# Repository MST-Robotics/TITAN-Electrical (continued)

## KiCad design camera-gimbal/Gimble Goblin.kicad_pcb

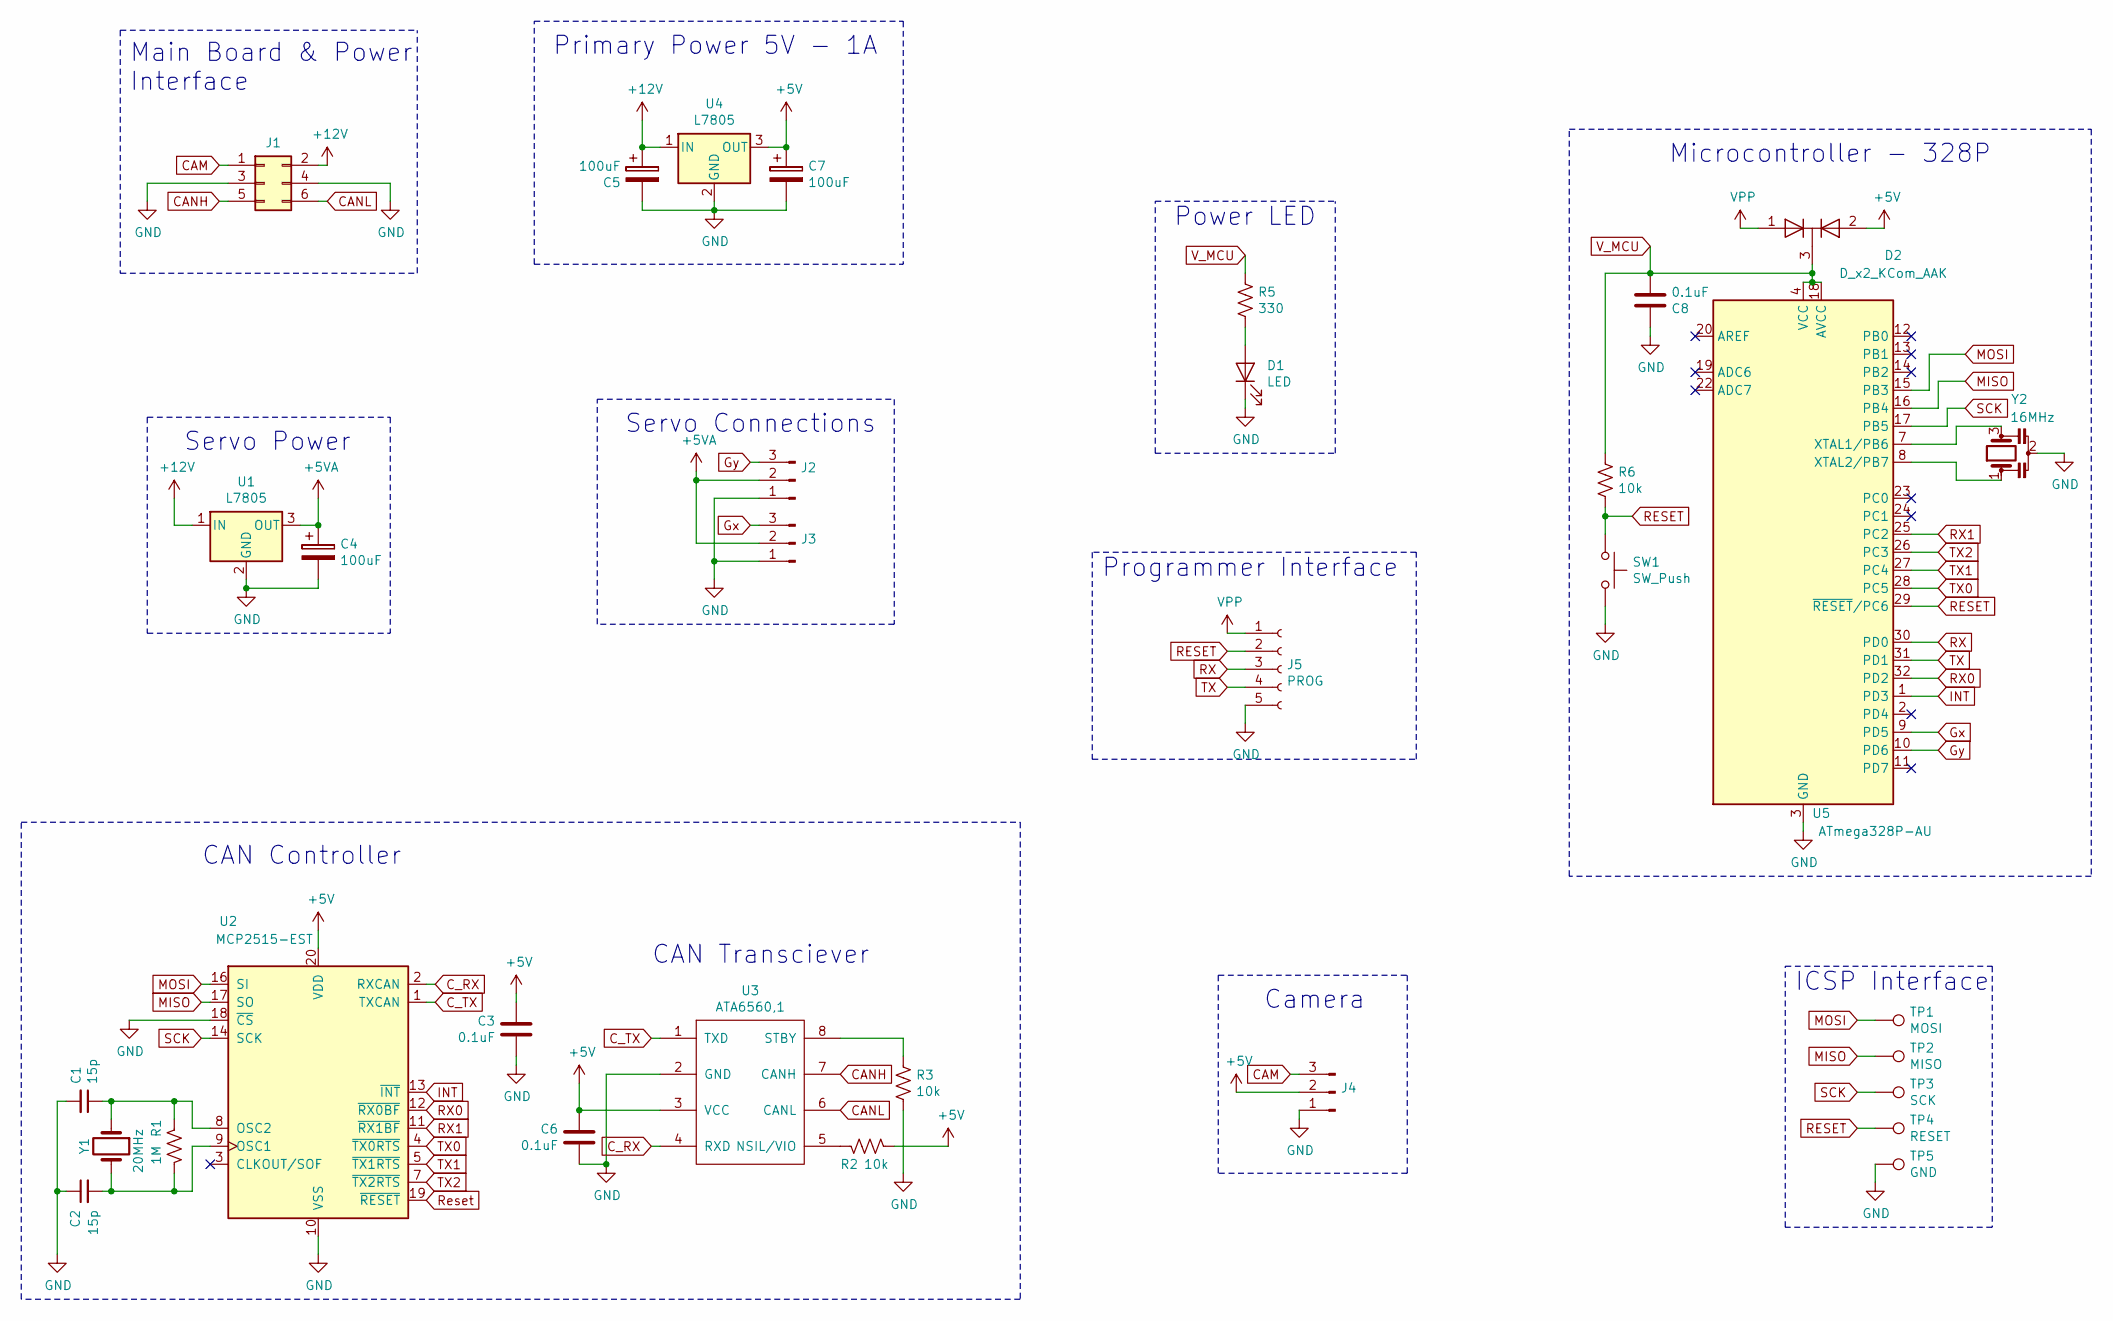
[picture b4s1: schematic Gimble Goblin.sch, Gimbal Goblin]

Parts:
C1, C2: 15p; C_0603_1608Metric
C3, C6, C8: 0.1uF; C_0603_1608Metric
C4, C5, C7: 100uF; CP_Radial_D5.0mm_P2.50mm
D1: LED; LED_0603_1608Metric
D2: D_x2_KCom_AAK; SOT-23
J1: Conn_02x03_Odd_Even; PinHeader_2x03_P2.54mm_Vertical
J2, J3, J4: Conn_01x03_Male; PinHeader_1x03_P2.54mm_Vertical
J5: PROG; PinHeader_1x05_P2.54mm_Vertical
R1: 1M; R_0603_1608Metric
R2, R3, R6: 10k; R_0603_1608Metric
R5: 330; R_0603_1608Metric
SW1: SW_Push; SW_PUSH_6mm
TP1: MOSI; TestPoint_Pad_D1.0mm
TP2: MISO; TestPoint_Pad_D1.0mm
TP3: SCK; TestPoint_Pad_D1.0mm
TP4: RESET; TestPoint_Pad_D1.0mm
TP5: GND; TestPoint_Pad_D1.0mm
U1, U4: L7805; SOT-223
U2: MCP2515-EST; TSSOP-20_4.4x6.5mm_P0.65mm
U3: ATA6560,1; SOIC-8_3.9x4.9mm_P1.27mm
U5: ATmega328P-AU; TQFP-32_7x7mm_P0.8mm
Y1: 20MHz; Crystal_SMD_0603-2Pin_6.0x3.5mm
Y2: 16MHz; OSC_CSTCE16M0V53-R0

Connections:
+5V: C3.2, C6.2, C7.1, D2.2 (A), J4.2, R2.1, U2.20 (VDD), U3.3 (VCC), U4.3 (OUT)
+5VA: C4.1, J2.2, J3.2, U1.3 (OUT)
+12V: C5.1, J1.2, U1.1 (IN), U4.1 (IN)
CAM: J1.1, J4.3
CANH: J1.5, U3.7 (CANH)
CANL: J1.6, U3.6 (CANL)
C_RX: U2.2 (RXCAN), U3.4 (RXD)
C_TX: U2.1 (TXCAN), U3.1 (TXD)
GND: C1.2, C2.1, C3.1, C4.2, C5.2, C6.1, C7.2, C8.2, D1.1 (K), J1.3, J1.4, J2.1, J3.1, J4.1, J5.5, R3.2, SW1.2, TP5.1, U1.2 (GND), U2.10 (VSS), U2.18 (~CS), U3.2 (GND), U4.2 (GND), U5.3 (GND), U5.5 (GND), U5.21 (GND), Y2.2
Gx: J3.3, U5.9 (PD5)
Gy: J2.3, U5.10 (PD6)
INT: U2.13 (~INT), U5.1 (PD3)
MISO: TP2.1, U2.17 (SO), U5.16 (PB4)
MOSI: TP1.1, U2.16 (SI), U5.15 (PB3)
unnamed: C1.1, R1.2, U2.8 (OSC2), Y1.1
unnamed: C2.2, R1.1, U2.9 (OSC1), Y1.2
unnamed: D1.2 (A), R5.2
unnamed: R2.2, U3.5 (NSIL/VIO)
unnamed: R3.1, U3.8 (STBY)
unnamed: U5.7 (XTAL1/PB6), Y2.3
unnamed: U5.8 (XTAL2/PB7), Y2.1
RESET: J5.2, R6.2, SW1.1, TP4.1, U5.29 (~RESET~/PC6)
RX: J5.3, U5.30 (PD0)
RX0: U2.12 (~RX0BF), U5.32 (PD2)
RX1: U2.11 (~RX1BF), U5.25 (PC2)
Reset: U2.19 (~RESET)
SCK: TP3.1, U2.14 (SCK), U5.17 (PB5)
TX: J5.4, U5.31 (PD1)
TX0: U2.4 (~TX0RTS), U5.28 (PC5)
TX1: U2.5 (~TX1RTS), U5.27 (PC4)
TX2: U2.7 (~TX2RTS), U5.26 (PC3)
VPP: D2.1 (A), J5.1
V_MCU: C8.1, D2.3 (K), R5.1, R6.1, U5.4 (VCC), U5.6 (VCC), U5.18 (AVCC)

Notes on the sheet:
Servo Connections
Camera
CAN Controller
CAN Transciever
Main Board & Power Interface
Primary Power 5V - 1A
Servo Power
Microcontroller - 328P
Power LED
Programmer Interface
ICSP Interface

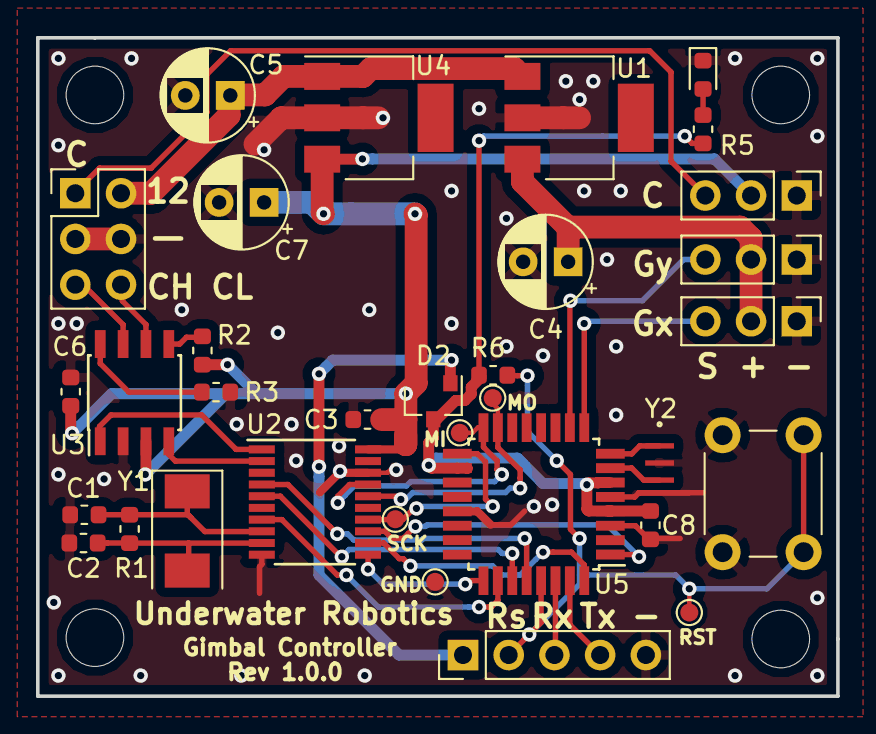
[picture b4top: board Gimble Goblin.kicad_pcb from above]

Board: 2 copper layers, 44.5 x 36.6 mm, 33 parts (0 on the bottom side), 32 nets.

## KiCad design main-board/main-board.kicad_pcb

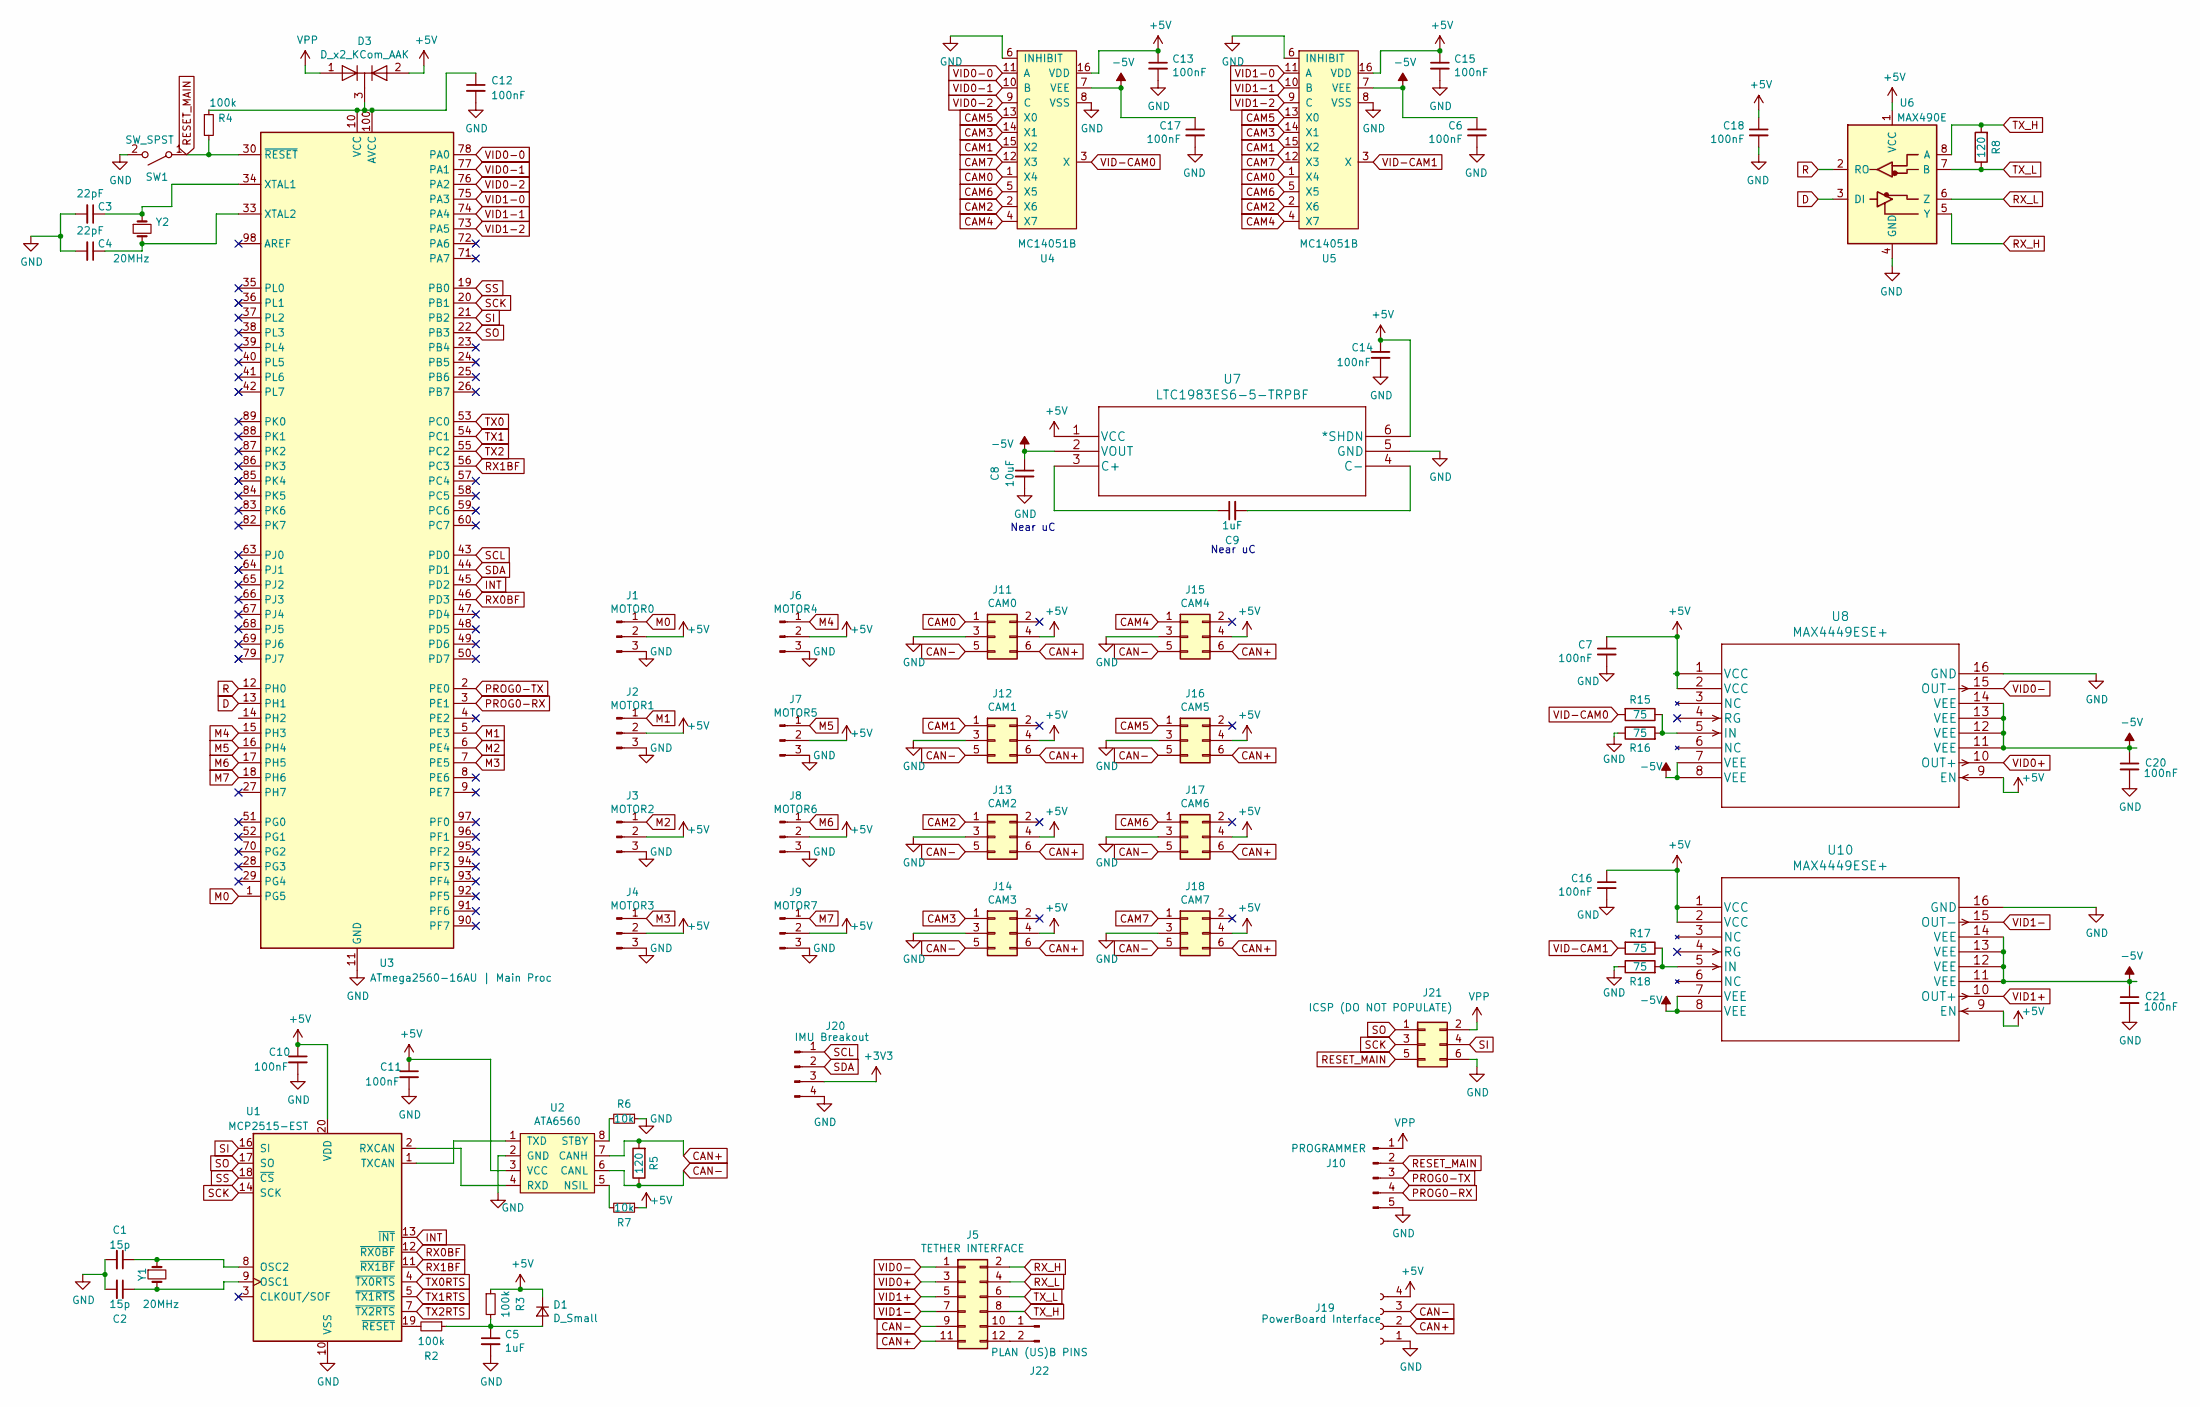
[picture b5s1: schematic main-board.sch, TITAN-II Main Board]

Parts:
C1, C2: 15p; C_0603_1608Metric
C3, C4: 22pF; C_0603_1608Metric
C5, C9: 1uF; C_0603_1608Metric
C6, C7, C10, C11, C12, C13, C14, C15, C16, C17, C18, C20, C21: 100nF; C_0603_1608Metric
C8: 10uF; C_0603_1608Metric
D1: D_Small; D_0603_1608Metric
D3: D_x2_KCom_AAK; SOT-23
J1: MOTOR0; PinHeader_1x03_P2.54mm_Vertical
J2: MOTOR1; PinHeader_1x03_P2.54mm_Vertical
J3: MOTOR2; PinHeader_1x03_P2.54mm_Vertical
J4: MOTOR3; PinHeader_1x03_P2.54mm_Vertical
J5: TETHER INTERFACE; PinHeader_2x06_P2.54mm_Vertical
J6: MOTOR4; PinHeader_1x03_P2.54mm_Vertical
J7: MOTOR5; PinHeader_1x03_P2.54mm_Vertical
J8: MOTOR6; PinHeader_1x03_P2.54mm_Vertical
J9: MOTOR7; PinHeader_1x03_P2.54mm_Vertical
J10: PROGRAMMER; PinHeader_1x05_P2.54mm_Vertical
J11: CAM0; PinHeader_2x03_P2.54mm_Vertical
J12: CAM1; PinHeader_2x03_P2.54mm_Vertical
J13: CAM2; PinHeader_2x03_P2.54mm_Vertical
J14: CAM3; PinHeader_2x03_P2.54mm_Vertical
J15: CAM4; PinHeader_2x03_P2.54mm_Vertical
J16: CAM5; PinHeader_2x03_P2.54mm_Vertical
J17: CAM6; PinHeader_2x03_P2.54mm_Vertical
J18: CAM7; PinHeader_2x03_P2.54mm_Vertical
J19: PowerBoard Interface; PinSocket_1x04_P2.54mm_Vertical
J20: IMU Breakout; PinHeader_1x04_P2.54mm_Vertical
J21: ICSP (DO NOT POPULATE); PinHeader_2x03_P1.00mm_Vertical
J22: PLAN (US)B PINS; PinHeader_1x02_P2.54mm_Vertical
R2, R3, R4: 100k; R_0603_1608Metric
R5, R8: 120; R_0603_1608Metric
R6, R7: 10k; R_0603_1608Metric
R15, R16, R17, R18: 75; R_0603_1608Metric
SW1: SW_SPST; SW_Tactile_Straight_KSA0Axx1LFTR
U1: MCP2515-EST; TSSOP-20_4.4x6.5mm_P0.65mm
U2: ATA6560; SOIC-8_3.9x4.9mm_P1.27mm
U3: ATmega2560-16AU | Main Proc; TQFP-100_14x14mm_P0.5mm
U4, U5: MC14051B; SOIC-16_3.9x9.9mm_P1.27mm
U6: MAX490E; SOIC-8_3.9x4.9mm_P1.27mm
U7: LTC1983ES6-5-TRPBF; SOT-23-6
U8, U10: MAX4449ESE+; MAX4449ESE&plus_
Y1, Y2: 20MHz; Crystal_SMD_Abracon_ABM7-2Pin_6.0x3.5mm

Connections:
+3V3: J20.3
+5V: C7.1, C10.1, C11.1, C13.1, C14.1, C15.1, C16.1, C18.1, D1.1 (K), D3.2 (A), J1.2, J2.2, J3.2, J4.2, J6.2, J7.2, J8.2, J9.2, J11.4, J12.4, J13.4, J14.4, J15.4, J16.4, J17.4, J18.4, J19.4, R3.1, R7.1, U1.20 (VDD), U2.3 (VCC), U4.16 (VDD), U5.16 (VDD), U6.1 (VCC), U7.1 (VCC), U7.6 (*SHDN), U8.1 (VCC), U8.2 (VCC), U8.9 (EN), U10.1 (VCC), U10.2 (VCC), U10.9 (EN)
-5V: C6.1, C8.1, C17.1, C20.1, C21.1, U4.7 (VEE), U5.7 (VEE), U7.2 (VOUT), U8.7 (VEE), U8.8 (VEE), U8.11 (VEE), U8.12 (VEE), U8.13 (VEE), U8.14 (VEE), U10.7 (VEE), U10.8 (VEE), U10.11 (VEE), U10.12 (VEE), U10.13 (VEE), U10.14 (VEE)
CAM0: J11.1, U4.1 (X4), U5.1 (X4)
CAM1: J12.1, U4.15 (X2), U5.15 (X2)
CAM2: J13.1, U4.2 (X6), U5.2 (X6)
CAM3: J14.1, U4.14 (X1), U5.14 (X1)
CAM4: J15.1, U4.4 (X7), U5.4 (X7)
CAM5: J16.1, U4.13 (X0), U5.13 (X0)
CAM6: J17.1, U4.5 (X5), U5.5 (X5)
CAM7: J18.1, U4.12 (X3), U5.12 (X3)
CAN+: J5.11, J11.6, J12.6, J13.6, J14.6, J15.6, J16.6, J17.6, J18.6, J19.2, R5.2, U2.7 (CANH)
CAN-: J5.9, J11.5, J12.5, J13.5, J14.5, J15.5, J16.5, J17.5, J18.5, J19.3, R5.1, U2.6 (CANL)
D: U3.13 (PH1), U6.3 (DI)
GND: C1.2, C2.2, C3.2, C4.2, C5.2, C6.2, C7.2, C8.2, C10.2, C11.2, C12.2, C13.2, C14.2, C15.2, C16.2, C17.2, C18.2, C20.2, C21.2, J1.3, J2.3, J3.3, J4.3, J6.3, J7.3, J8.3, J9.3, J10.5, J11.3, J12.3, J13.3, J14.3, J15.3, J16.3, J17.3, J18.3, J19.1, J20.4, J21.6, R6.1, R16.1, R18.1, SW1.2 (B), U1.10 (VSS), U2.2 (GND), U3.11 (GND), U3.32 (GND), U3.62 (GND), U3.81 (GND), U3.99 (GND), U4.6 (INHIBIT), U4.8 (VSS), U5.6 (INHIBIT), U5.8 (VSS), U6.4 (GND), U7.5 (GND), U8.16 (GND), U10.16 (GND)
INT: U1.13 (~INT), U3.45 (PD2)
M0: J1.1, U3.1 (PG5)
M1: J2.1, U3.5 (PE3)
M2: J3.1, U3.6 (PE4)
M3: J4.1, U3.7 (PE5)
M4: J6.1, U3.15 (PH3)
M5: J7.1, U3.16 (PH4)
M6: J8.1, U3.17 (PH5)
M7: J9.1, U3.18 (PH6)
unnamed: C1.1, U1.8 (OSC2), Y1.1
unnamed: C2.1, U1.9 (OSC1), Y1.2
unnamed: C3.1, U3.34 (XTAL1), Y2.1
unnamed: C4.1, U3.33 (XTAL2), Y2.2
unnamed: C5.1, D1.2 (A), R2.1, R3.2
unnamed: C9.1, U7.3 (C+)
unnamed: C9.2, U7.4 (C-)
unnamed: C12.1, D3.3 (K), R4.1, U3.10 (VCC), U3.31 (VCC), U3.61 (VCC), U3.80 (VCC), U3.100 (AVCC)
unnamed: J5.10, J22.1
unnamed: J5.12, J22.2
unnamed: R2.2, U1.19 (~RESET)
unnamed: R6.2, U2.8 (STBY)
unnamed: R7.2, U2.5 (NSIL)
unnamed: R15.1, R16.2, U8.5 (IN)
unnamed: R17.1, R18.2, U10.5 (IN)
unnamed: U1.1 (TXCAN), U2.1 (TXD)
unnamed: U1.2 (RXCAN), U2.4 (RXD)
PROG0-RX: J10.4, U3.3 (PE1)
PROG0-TX: J10.3, U3.2 (PE0)
R: U3.12 (PH0), U6.2 (RO)
RESET_MAIN: J10.2, J21.5, R4.2, SW1.1 (A), U3.30 (~RESET)
RX0BF: U1.12 (~RX0BF), U3.46 (PD3)
RX1BF: U1.11 (~RX1BF), U3.56 (PC3)
RX_H: J5.2, U6.5 (Y)
RX_L: J5.4, U6.6 (Z)
SCK: J21.3, U1.14 (SCK), U3.20 (PB1)
SCL: J20.1, U3.43 (PD0)
SDA: J20.2, U3.44 (PD1)
SI: J21.4, U1.16 (SI), U3.21 (PB2)
SO: J21.1, U1.17 (SO), U3.22 (PB3)
SS: U1.18 (~CS), U3.19 (PB0)
TX0: U3.53 (PC0)
TX0RTS: U1.4 (~TX0RTS)
TX1: U3.54 (PC1)
TX1RTS: U1.5 (~TX1RTS)
TX2: U3.55 (PC2)
TX2RTS: U1.7 (~TX2RTS)
TX_H: J5.8, R8.2, U6.8 (A)
TX_L: J5.6, R8.1, U6.7 (B)
VID0+: J5.3, U8.10 (OUT+)
VID0-: J5.1, U8.15 (OUT-)
VID0-0: U3.78 (PA0), U4.11 (A)
VID0-1: U3.77 (PA1), U4.10 (B)
VID0-2: U3.76 (PA2), U4.9 (C)
VID1+: J5.5, U10.10 (OUT+)
VID1-: J5.7, U10.15 (OUT-)
VID1-0: U3.75 (PA3), U5.11 (A)
VID1-1: U3.74 (PA4), U5.10 (B)
VID1-2: U3.73 (PA5), U5.9 (C)
VID-CAM0: R15.2, U4.3 (X)
VID-CAM1: R17.2, U5.3 (X)
VPP: D3.1 (A), J10.1, J21.2

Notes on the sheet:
Near uC

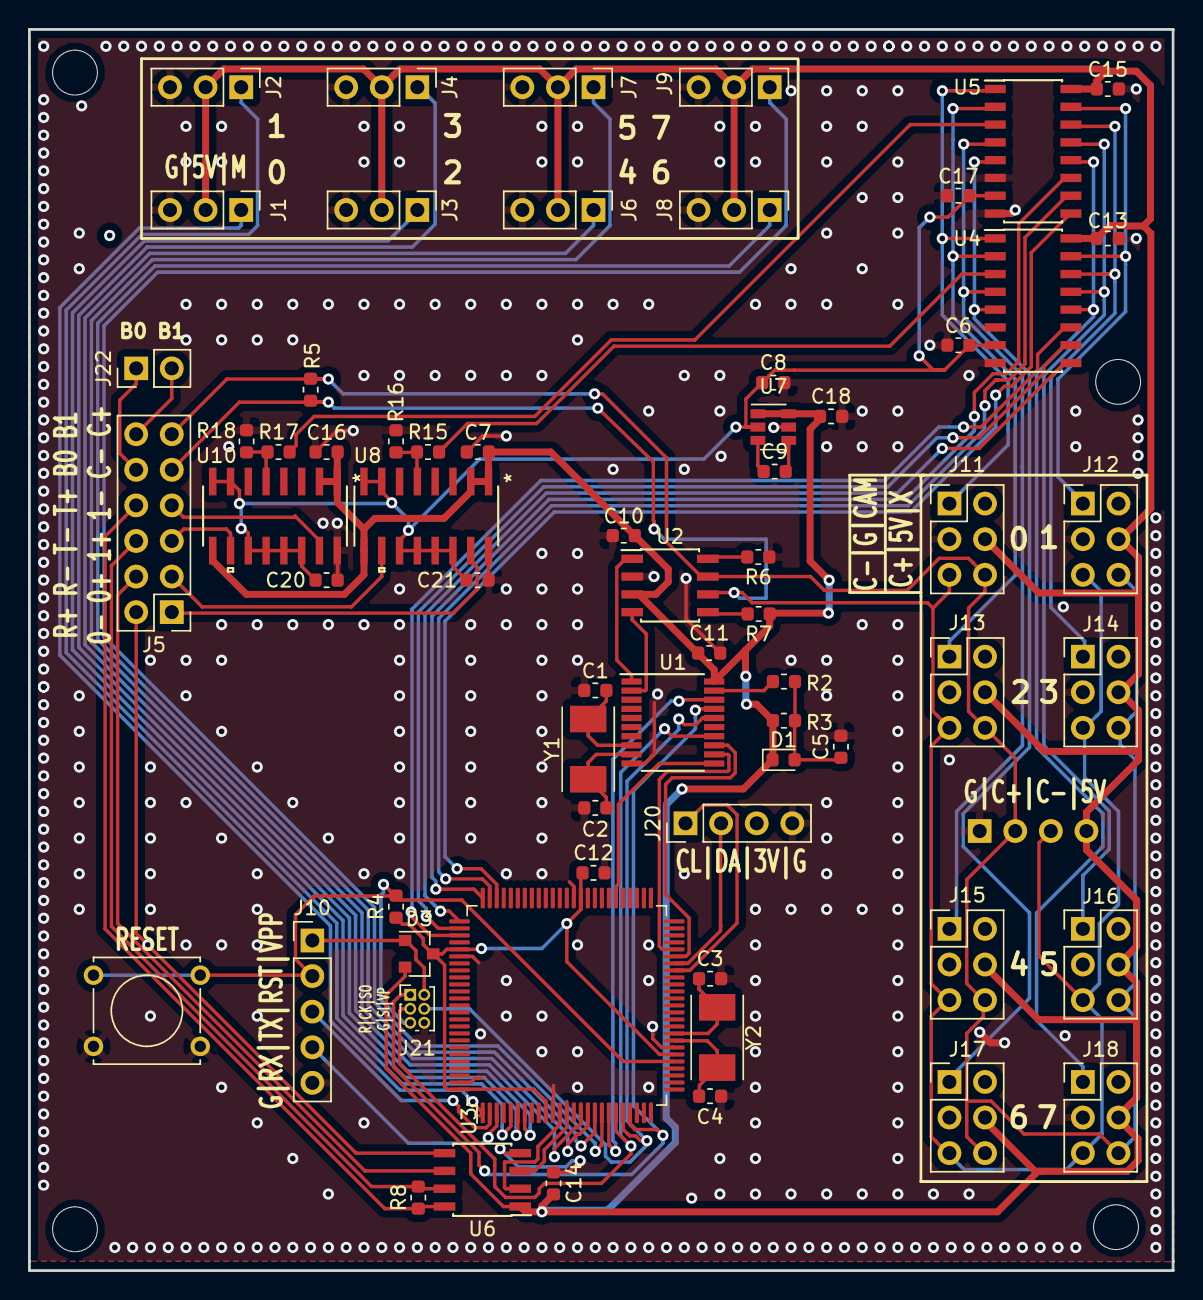
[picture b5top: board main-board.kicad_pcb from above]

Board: 2 copper layers, 81.6 x 88.6 mm, 67 parts (1 on the bottom side), 69 nets.

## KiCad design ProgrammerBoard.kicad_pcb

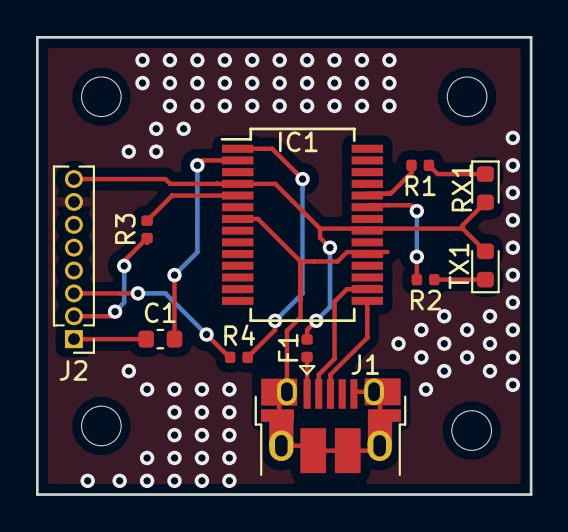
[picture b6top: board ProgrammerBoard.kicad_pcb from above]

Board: 2 copper layers, 27.4 x 25.4 mm, 11 parts (0 on the bottom side), 15 nets.

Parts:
C1: 100nF; C_0603_1608Metric
F1: 500mA; Fuse_0402_1005Metric
IC1: FT232RL; SSOP-28_5.3x10.2mm_P0.65mm
J1: USB_B_Micro; USB_Micro-B_Amphenol_10103594-0001LF_Horizontal
J2: Jumper_For_RJ45; PinHeader_1x08_P1.27mm_Vertical
R1, R2: 1K; R_0402_1005Metric
R3, R4: 100; R_0402_1005Metric
RX1: Blue; LED_0603_1608Metric
TX1: Green; LED_0603_1608Metric

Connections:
+5V: F1.1, IC1.4, IC1.20, J2.8, RX1.2, TX1.2
Earth: IC1.7, IC1.18, IC1.21, IC1.25, IC1.26, J1.5, J1.6
unnamed: C1.1, J2.1
unnamed: C1.2, IC1.2
unnamed: F1.2, J1.1
unnamed: IC1.1, R4.2
unnamed: IC1.5, R3.2
unnamed: IC1.15, J1.3
unnamed: IC1.16, J1.2
unnamed: IC1.22, R2.2
unnamed: IC1.23, R1.2
unnamed: J2.2, R3.1
unnamed: J2.3, R4.1
unnamed: R1.1, RX1.1
unnamed: R2.1, TX1.1

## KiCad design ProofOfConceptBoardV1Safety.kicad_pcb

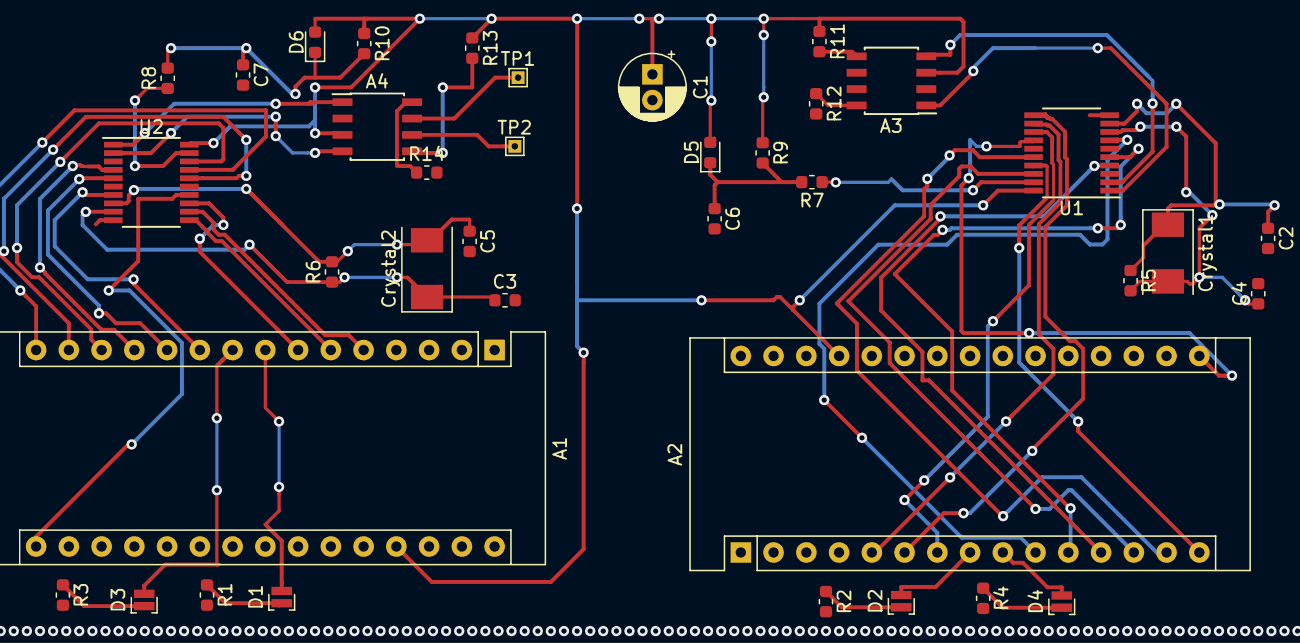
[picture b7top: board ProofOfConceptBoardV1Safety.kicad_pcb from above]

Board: 2 copper layers, 37 parts (0 on the bottom side), 49 nets.

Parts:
A1, A2: Arduino_Nano_v3.x; Arduino_Nano
A3, A4: ATA6560; SOIC-8_3.9x4.9mm_P1.27mm
C1: 100uF; CP_Radial_D5.0mm_P2.00mm
C2, C3, C4, C5: 15pF; C_0603_1608Metric
C6, C7: 1uF; C_0603_1608Metric
Crystal1: 20MHz; Crystal_SMD_0603-2Pin_6.0x3.5mm
Crystal2: 20 MHz; Crystal_SMD_0603-2Pin_6.0x3.5mm
D1, D2, D3, D4: LED; LED_Cree-XQ
D5, D6: DIODE; D_0603_1608Metric
R1, R2, R3, R4: 220; R_0603_1608Metric
R5, R6: 1M; R_0603_1608Metric
R7, R8, R11, R12, R13, R14: 10k; R_0603_1608Metric
R9, R10: 100k; R_0603_1608Metric
TP1, TP2: TestPoint; TestPoint_THTPad_1.0x1.0mm_Drill0.5mm
U1, U2: MCP2515-EST; TSSOP-20_4.4x6.5mm_P0.65mm

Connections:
+5V: A1.27, A2.27, A3.3, A4.3, C1.1, D5.2, D6.2, R9.1, R10.1, R11.1, R13.1, U1.20, U2.20
CANRX: A3.4, U1.2
CANRX_2: A4.4, U2.2
CANTX: A3.1, U1.1
CANTX_2: A4.1, U2.1
GNDREF: A1.4, A1.18, A1.29, A2.4, A2.18, A2.29, A3.2, A4.2, C1.2, C2.2, C3.2, C4.2, C5.2, C6.2, C7.2, R1.2, R2.2, R3.2, R4.2, R12.2, R14.2, U1.10, U2.10
INT0: A2.5, U1.12
INT0_2: A1.5, U2.12
INT1: A2.6, U1.11
INT1_2: A1.6, U2.11
INTMCP: A2.7, U1.13
INTMCP_2: A1.7, U2.13
MISO: A2.15, U1.17
MISO_2: A1.15, U2.17
MOSI: A2.14, U1.16
MOSI_2: A1.14, U2.16
unnamed: A1.8, D1.2
unnamed: A1.9, D3.2
unnamed: A2.8, D2.2
unnamed: A2.9, D4.2
unnamed: A3.5, R11.2
unnamed: A3.8, R12.1
unnamed: A4.5, R13.2
unnamed: A4.6, TP2.1
unnamed: A4.7, TP1.1
unnamed: A4.8, R14.1
unnamed: C6.1, D5.1, R7.2, R9.2
unnamed: C7.1, D6.1, R8.2, R10.2
unnamed: D1.1, R1.1
unnamed: D2.1, R2.1
unnamed: D3.1, R3.1
unnamed: D4.1, R4.1
unnamed: R7.1, U1.19
unnamed: R8.1, U2.19
OSC1: C2.1, Crystal1.1, R5.1, U1.9
OSC1_2: C3.1, Crystal2.1, R6.1, U2.9
OSC2: C4.1, Crystal1.2, R5.2, U1.8
OSC2_2: C5.1, Crystal2.2, R6.2, U2.8
SCK: A2.16, U1.14
SCK_2: A1.16, U2.14
SS: A2.13, U1.18
SS_2: A1.13, U2.18
TBUF0: A2.10, U1.7
TBUF0_2: A1.10, U2.7
TBUF1: A2.11, U1.5
TBUF1_2: A1.11, U2.5
TBUF2: A2.12, U1.4
TBUF2_2: A1.12, U2.4
VCC: A1.30, A2.30

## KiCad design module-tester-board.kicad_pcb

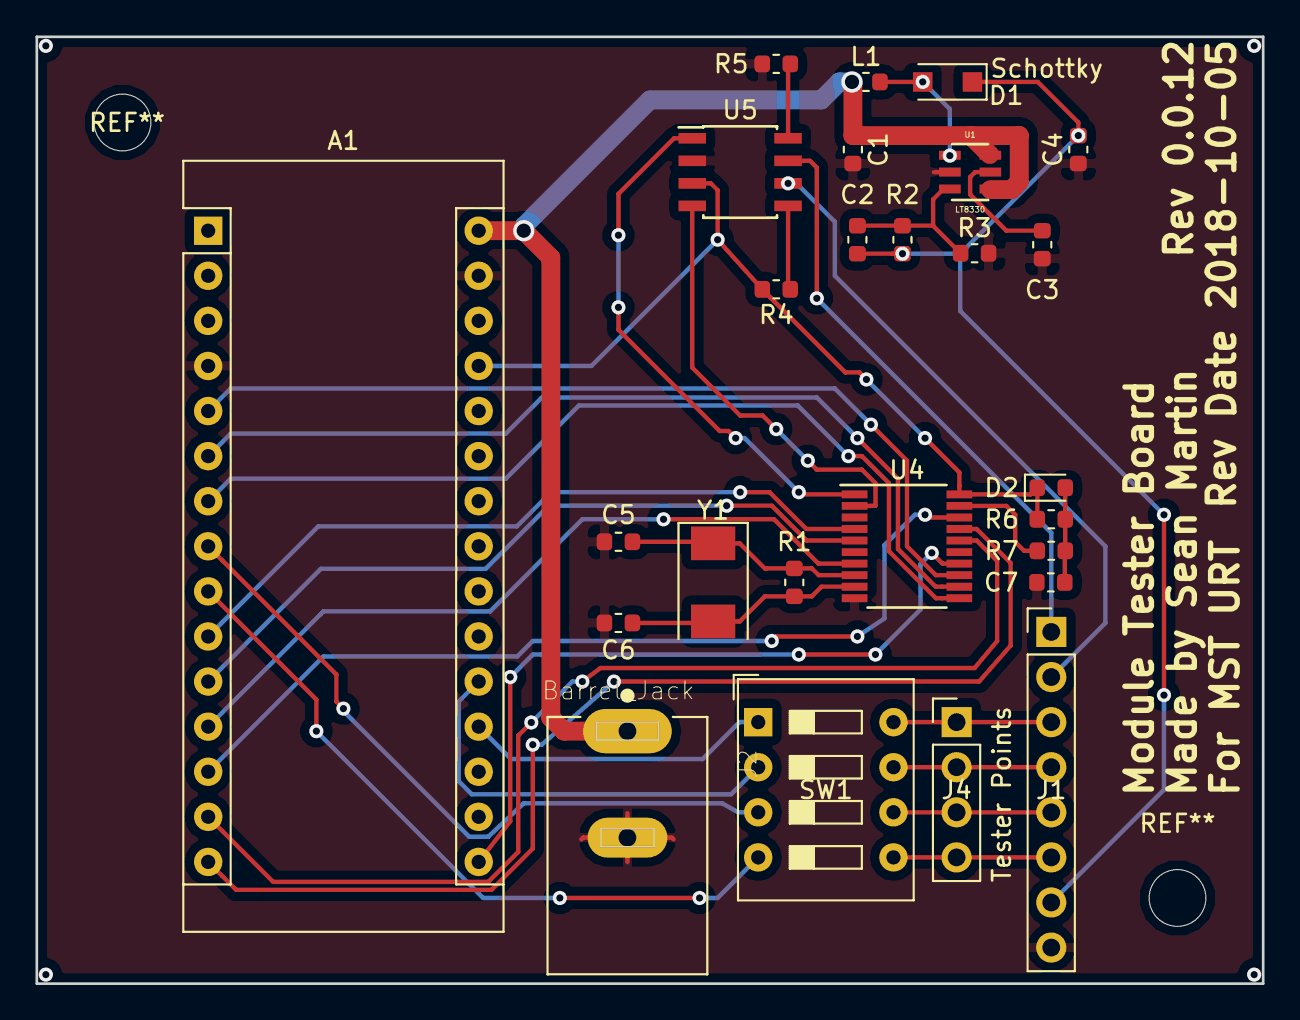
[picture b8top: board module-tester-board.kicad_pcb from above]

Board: 2 copper layers, 69.1 x 53.3 mm, 26 parts (0 on the bottom side), 35 nets.

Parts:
A1: Arduino_Nano_v3.x; Arduino_Nano
C1, C4: 4.7u; C_0603_1608Metric
C2: 4.7p; C_0603_1608Metric
C3: 1u; C_0603_1608Metric
C5, C6: 15p; C_0603_1608Metric
C7: 1uF; C_0603_1608Metric
D1: Schottky; D_SOD-123F
D2: 1N4007; D_0603_1608Metric
J1: PinHeader_1x08_P2.54mm_Vertical
J2: Barrel_Jack; CUI_PJ-037A
J4: Tester Points; PinHeader_1x04_P2.54mm_Vertical
L1: 6.8u; L_0603_1608Metric
R1, R2: 1M; R_0603_1608Metric
R3: 34.8k; R_0603_1608Metric
R4, R5, R7: 10k; R_0603_1608Metric
R6: 100k; R_0603_1608Metric
SW1: SW_DIP_SPSTx04_Slide_9.78x12.34mm_W7.62mm_P2.54mm
U1: LT8330; TSOT-23_S6
U4: MCP2515; TSSOP-20_4.4x6.5mm_P0.65mm
U5: ATA6560,1; SOIC-8_3.9x4.9mm_P1.27mm
Y1: 20MHz; Crystal_SMD_0603-2Pin_6.0x3.5mm

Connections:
+5V: A1.27, D2.1, R4.2, R6.1, U4.20, U5.3
+12V: A1.30, C1.1, J2.1, L1.1, U1.4, U1.6
+48V: C2.1, C4.2, D1.1, J1.7, R2.1
A0: A1.19, SW1.1
A1: A1.20, SW1.2
CANH: J1.1, U5.7
CANL: J1.2, U5.6
GND: A1.4, A1.29, C1.2, C3.2, C4.1, C5.2, C6.1, C7.2, J1.8, J2.2, R3.2, R5.2, U1.2, U4.10, U5.2
INT: A1.5, U4.13
unnamed: C2.2, R2.2, R3.1, U1.3
unnamed: C3.1, U1.5
unnamed: C5.1, R1.2, U4.8, Y1.1
unnamed: C6.2, R1.1, U4.9, Y1.2
unnamed: C7.1, D2.2, R6.2, R7.2
unnamed: D1.2, L1.2, U1.1
unnamed: J1.3, J4.1, SW1.8
unnamed: J1.4, J4.2, SW1.7
unnamed: J1.5, J4.3, SW1.6
unnamed: J1.6, J4.4, SW1.5
unnamed: R4.1, U5.5
unnamed: R5.1, U5.8
unnamed: U4.1, U5.1
unnamed: U4.2, U5.4
PWM0: A1.8, SW1.3
PWM1: A1.9, SW1.4
RX0: A1.6, U4.12
RX1: A1.7, U4.11
Reset: R7.1, U4.19
SCK: A1.16, U4.14
SI: A1.14, U4.16
SO: A1.15, U4.17
SS: A1.13, U4.18
TX0: A1.10, U4.4
TX1: A1.11, U4.5
TX2: A1.12, U4.7

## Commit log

2018-09-09 Add text test file
2018-09-09 Version 0.1
    Initial Commit. Schematic not complete.
2018-09-09 Version 0.0.1
    Initial Commit. Schematic not complete.
2018-09-09 Version 0.0.1
    Schematic for review
2018-09-09 Version 0.0.2
    Schematic to be Reviewed
2018-09-10 Add Motor Test Module
2018-09-10 Motor test module for stepper motors
2018-09-11 Adds programmer board files
2018-09-13 Begins part labeling
2018-09-13 Add servos
2018-09-14 First draft of motor test module
2018-09-17 Version 0.0.3
    Fixed red lines
2018-09-17 0.0.3 cleanup and change power symbols
2018-09-17 0.0.4 cleanup and change power symbols
2018-09-18 Second draft of Motor Test
2018-09-20 Added labels to programmer board
2018-09-20 Init design
2018-09-20 Picked out parts
2018-09-20 0.0.2 Picked Part
2018-09-20 0.0.1 Initial Commit
2018-09-21 Power circuits added to design
2018-09-21 Finishing up power system
2018-09-22 Added sensors and finished up design
2018-09-22 Added CAN support
2018-09-22 Started PCB Layout, assigning packages
2018-09-25 Redline updates
2018-09-26 finishing touches
2018-09-27 Footprint changes and Zener to Schottky
2018-09-27 0.0.7 change reset RC circuit
2018-09-27 0.0.7 change interrupt configuration for CAN IC
2018-09-29 Added board & traces
2018-09-30 fixed
2018-09-30 Make initial directory
2018-09-30 Add empty project
2018-09-30 upload pre- 0.0.1 WIP
2018-09-30 Update project definition
2018-09-30 Update again
2018-09-30 0.0.9 Add Barrel Jack
2018-10-01 Add RS485
2018-10-01 0.0.10 Switched switches, footprints, and start Board layout
2018-10-01 Finished adding power regulator isolation
2018-10-02 0.0.11 First version of traces
2018-10-02 Addition of power regulator
2018-10-03 0.0.2 Initial Commit
2018-10-04 0.0.2 Fixed Last Commit. Uploaded Schematic for Review.
2018-10-04 Board size optimization
2018-10-04 Add power regulator
2018-10-06 0.0.12 Fixed board trace and GND plane issues
2018-10-09 Add arduino mega
2018-10-10 PCB Layout work
2018-10-11 0.0.1
    First complete (?) schematic
2018-10-11 initial main-board commit
2018-10-11 remove backup
2018-10-11 Module Motor Test Draft
2018-10-11 Finished Rev 0.0.1
2018-10-11 HIgh power routing work
2018-10-12 Finished high power routing
2018-10-12 Current sensor routing/finishing touches
2018-10-12 working on microcontroller routing
2018-10-12 silkscreen
2018-10-13 finishing silkscreen
2018-10-13 Finished final Draft of design
2018-10-14 Added fuses
2018-10-15 B: 0.0.3 S: 0.0.10 12mil track and Gerber
2018-10-17 0.0.2 first egregious error
    The can interface wasn't connected to the arduino, now it is
2018-10-17 github is hard
    I lack the knowledge to properly manipulate files, this should be better now. it was previously a mess
2018-10-17 updated outline, added 3d file for ben
2018-10-18 Finished Rev 0.0.2
2018-10-18 add video, sans new balun
2018-10-18 add programming header
2018-10-18 add CAN
2018-10-18 post-board review edits
2018-10-18 done sans power
2018-10-18 ready for review
2018-10-19 0.0.3 First Complete Design - Ready for Review
2018-10-20 finished re-routing for v_prog diode
2018-10-20 Added 3d models, finished design
2018-10-21 capacitor updates
2018-10-21 new dxf
2018-10-21 removed stray trace
2018-10-21 added another moutning hole
2018-10-21 address review comments
2018-10-21 changed board outline
2018-10-21 removed extra hole
2018-10-21 updated step file
2018-10-21 0.0.3
    Schematic Fixes + PCB Layout
2018-10-21 Updated Schematic, PCB draft made and done, fixed a PCB Box
2018-10-21 Added new mouting holes for right hand side of pcb
2018-10-22 add description to readme
2018-10-23 annotate
2018-10-25 added new mounting holes for main board
2018-10-25 begin board
2018-10-26 Changed 5v input capacitor package
2018-10-27 populate components
2018-10-27 add traces for all signals except cameras
2018-10-29 complete electrical circuit, needs holes
2018-10-29 add mounting holes
2018-10-29 Review+changes- see description
    Schematic:
    * add ICSP connector
    * add VPP and diode D3for uC programming
    PCB:
    * add ICSP connector
    * add VPP diode
2018-10-29 Updated D2 package
2018-10-29 Generated gerber files
2018-10-29 Updated resistor sizes
2018-10-31 0.0.4 Fixed some PCB Connections and adjusted Top and Bot Ground Plane
2018-11-01 0.0.5 Changes to board after review. Also with og backup. Sch changes
2018-11-01 Various changes (see description)
    Schematic Changes:
    * add optional second RS485
    * add filter caps to IC power
    * remove input resistor on reset line of 2560
    * change CAN UART lines to be tx<>tx rx<>rx
    PCB Changes:
2018-11-01 S1.0.1 B1.0.1 See Desc
    * Reorganized video and motor connectors for easier ROV wiring
    * PCB Via redesign
2018-11-01 S1.0.0 B1.0.1 Update silkscreen for schematic/pcb version
2018-11-01 Slight silkscreen fix on motor connectors
2018-11-01 move datasheet to google drive
2018-11-02 S1.0.0 B1.0.0 (See Desc)
    * Add step
    * move gerbers
    * remove library
    * assign 3d models and generate step file
    * add more ground plane vias
2018-11-02 S1.0.1 B1.0.1
    Schematic:
    * Add filter cap for 5v
    * slight layout changes
    * change gndref symbols to gnd
    Board:
    * slight via rework
2018-11-02 Generate 3d model, gerbers, drills
2018-11-02 Re-organized schematic
    Fixed schematic,
    Updated PCB and compomnents
2018-11-03 Routed PCB
    Worked on silkscreen
    Finished all routing and via stiching
2018-11-03 S 1.0.1 B 1.0.1 change camera balancing to MAX4449ESE
2018-11-03 Implemented review fixes
    Generated step file,
    Generated gerber zip with drills,
    Also verified gerbers online
2018-11-03 Motor Test final schematic
2018-11-03 Cleaning up schematic
    Adding camera decoding
    created symbol library
2018-11-03 switching computers - wip
2018-11-03 Started component organization on PCB
    Added -5V regulator, and other camera decoding circuit
2018-11-04 Adding full deplex rs485
2018-11-04 Removing old routes to support full duplex rs485
2018-11-04 working on pcb layout
2018-11-04 pcb layout
2018-11-05 Reorganize files, generate drills and step
2018-11-05 See Description
    * Reorganized file system
    * Slight PCB rework
    * Generated gerbers/drills/3d model
2018-11-05 Finishing pcb routing
2018-11-05 CAN Test Board B1.0.1 Shrink to <10cm^2 for printing
2018-11-05 Finished PCB routing and silkscreen
    Created 3d model,
    Created gerber files
2018-11-05 S1.0.3 B1.0.3 See Desc
    * various layout changes
    * remove 0-ohm resistors on CAN
    * add RS485 full-duplex
    * add optional USB connection
    * change crystal footprint
    * I'm sure I've forgotten things sorry
2018-11-05 Added 5v Regulator
    Moved some parts to add additonal pin
2018-11-05 Replaced moutning holes drawn in edge cuts with real holes and regenerated all gerbers
2018-11-05 removed extra files
2018-11-05 Remove control-station-board form master because I suck at git
2018-11-05 I really suck at Git
2018-11-06 Exported gerber files for surface control board
2018-11-06 Fix some git BS
2018-11-08 beginning layout
2018-11-14 First draft of layout
2018-11-17 Second draft of layout
2018-11-21 Fixed water ingress shutoff signal control
2018-11-21 selected new footprint for BJT for power shutoff
2018-11-22 Adding 3.3v regulator hardware for TC amps
2018-11-22 Adding level shifting for TC amp
2018-11-22 Fixed 600W regulator symbol issue. Re-routed output planes.
    Also finished implementing level shifting for SPI
2018-11-22 Fixed board outline issues, added screw terminals for TCs
2018-11-22 Removed solder jumper for level shifter OE pin. Fixed clearance issue on B.cu layer
2018-11-25 fixed silkscreen issue for TC polarity on screw terminals
2018-11-25 Fixed a power trace to one of the current sensors.
2018-11-29 Third draft of layout
2018-12-05 add microcontroller shutoff circuit
2018-12-06 Fourth draft of layout
2018-12-06 Fifth draft of layout
2018-12-08 Sixth draft of layout
2019-02-02 final draft
2019-02-02 Add logo
2019-02-02 fixed stuff
2019-05-22 begin new servo board design
